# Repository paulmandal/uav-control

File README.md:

# UAV Control Link

This project is a UAV control link over a serial modem using a PlayStation 3 controller as an input.  The software produces a PPM signal output on the UAV board that can be read by typical UAV boards.

# Requirements

- [Arduino](https://www.arduino.cc/en/Main/Software)
- [Eagle](https://www.autodesk.com/products/eagle/free-download)

# Table of Contents

| Directory | Contents |
|---|----|
| js_ctrl | Takes PlayStation 3 controller input, updates its model of the airframe, relays the airframe state to joystick2ppm |
| joystick2ppm | Listens to serial traffic from js_ctrl, outputs a PPM signal based on the servo states, handles handshaking and sync |
| gcs_relay | Ground control station relay - relays traffic from js_ctrl to a serial modem |
| servotest | Decodes a PPM signal into servo outputs |

# Disclaimer

This code is old, umaintained, and probably kinda slow depending on your serial modem.  I wouldn't recommend using this to fly anything, but maybe some lessons can be learned from the code.

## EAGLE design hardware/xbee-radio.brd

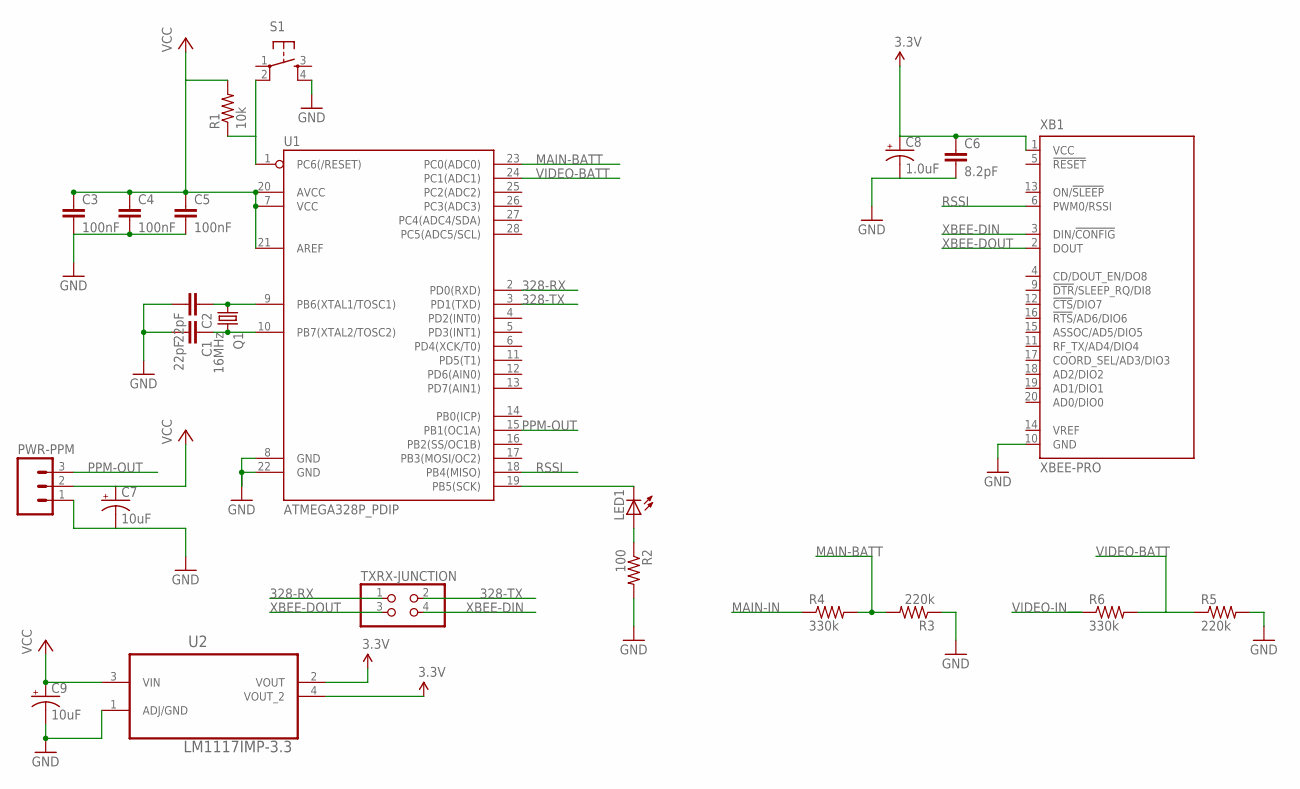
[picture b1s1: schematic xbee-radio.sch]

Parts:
C1, C2: 22pF; C2.5-2
C3, C4, C5: 100nF; C2.5-2
C6: 8.2pF; C2.5-2
C7, C9: 10uF; E2-5
C8: 1.0uF; E2-5
LED1: LED3MM
PWR-PPM: M03PTH; 1X03
Q1: 16MHz; TC26V
R1: 10k; 0204/5
R2: 100; 0204/5
R3, R5: 220k; 0204/5
R4, R6: 330k; 0204/5
S1: TAC_SWITCHPTH; TACTILE-PTH
TXRX-JUNCTION: PINHD-2X2; 2X02
U1: ATMEGA328P_PDIP; DIL28-3
U2: LM1117IMP-3.3; SOT230P696X180-4N
XB1: XBEE-PRO

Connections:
3.3V: C6.1, C8.+, U2.2 (VOUT), U2.4 (VOUT_2), XB1.1 (VCC)
328-RX: TXRX-JUNCTION.1, U1.2 (PD0(RXD))
328-TX: TXRX-JUNCTION.2, U1.3 (PD1(TXD))
GND: C1.2, C2.2, C3.2, C4.2, C5.2, C6.2, C7.-, C8.-, C9.-, PWR-PPM.1, R2.2, R3.1, R5.2, S1.4, U1.8 (GND), U1.22 (GND), U2.1 (ADJ/GND), XB1.10 (GND)
MAIN-BATT: R3.2, R4.2, U1.23 (PC0(ADC0))
MAIN-IN: R4.1
unnamed: R1.1, S1.2, U1.1 (PC6(/RESET))
unnamed: C1.1, Q1.2, U1.10 (PB7(XTAL2/TOSC2))
unnamed: C2.1, Q1.1, U1.9 (PB6(XTAL1/TOSC1))
unnamed: LED1.K (C), U1.19 (PB5(SCK))
unnamed: LED1.A, R2.1
PPM-OUT: PWR-PPM.3, U1.15 (PB1(OC1A))
RSSI: U1.18 (PB4(MISO)), XB1.6 (PWM0/RSSI)
VCC: C3.1, C4.1, C5.1, C7.+, C9.+, PWR-PPM.2, R1.2, U1.7 (VCC), U1.20 (AVCC), U1.21 (AREF), U2.3 (VIN)
VIDEO-BATT: R5.1, R6.2, U1.24 (PC1(ADC1))
VIDEO-IN: R6.1
XBEE-DIN: TXRX-JUNCTION.4, XB1.3 (DIN/!CONFIG)
XBEE-DOUT: TXRX-JUNCTION.3, XB1.2 (DOUT)

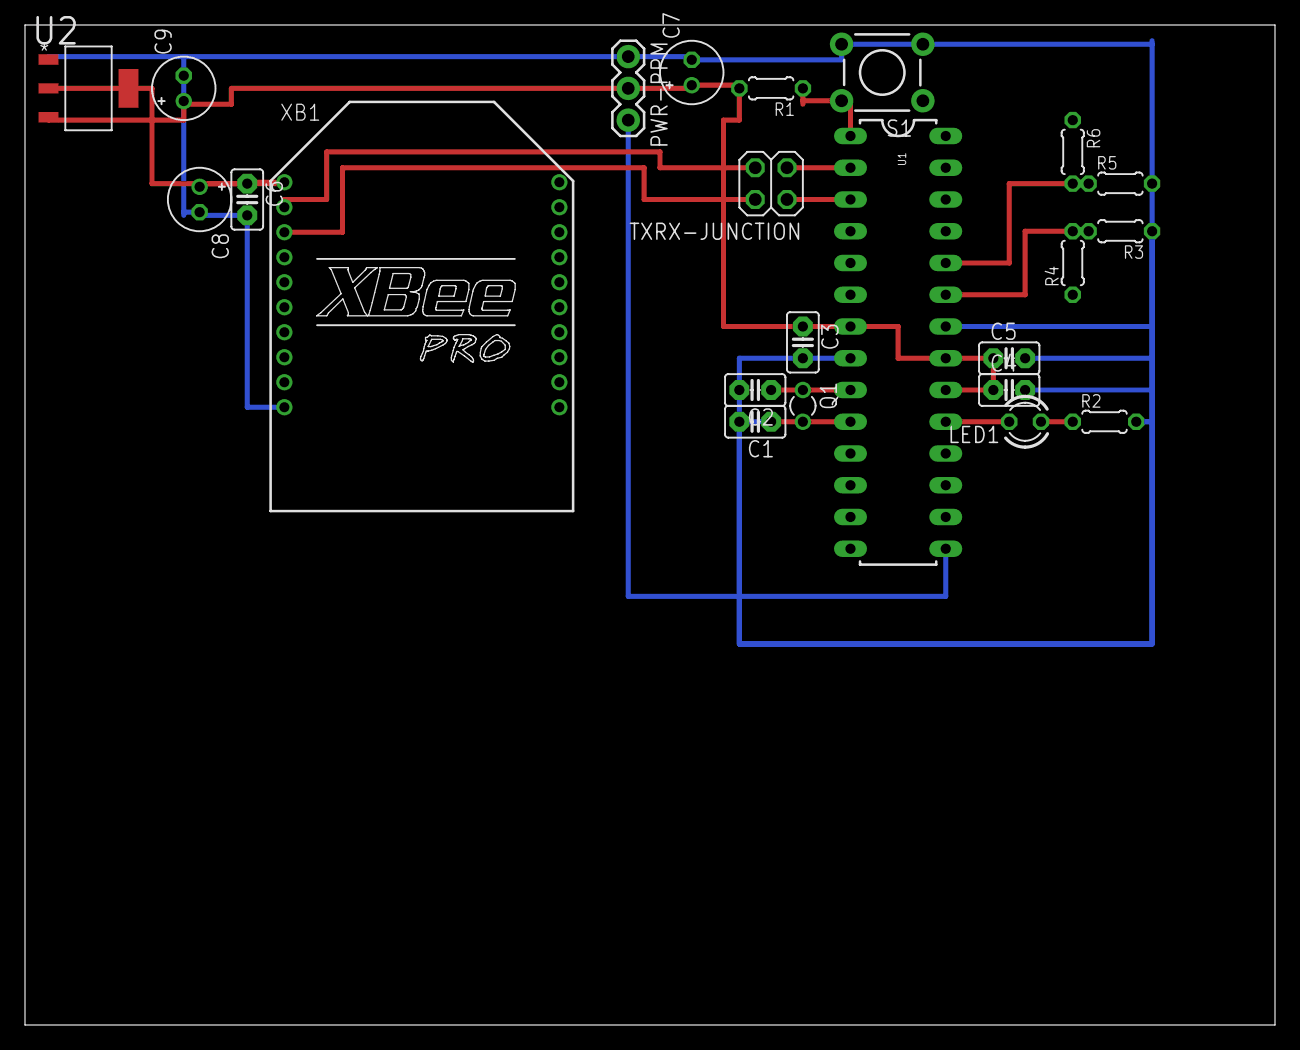
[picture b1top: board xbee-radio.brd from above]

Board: 2 copper layers, 100.0 x 80.0 mm, 23 parts (0 on the bottom side), 16 nets.

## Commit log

2011-03-24 Added main C file
2011-03-24 Added necessary .h file from jstest package
2011-03-25 Last night's build
2011-03-25 Remix\!
2011-03-26 Rewrote code.. Works now
2011-03-26 Trying to get checksum to work.. not sure
2011-03-26 Continuing, checksum in place
2011-03-30 Added latest joystick2ppm (2.0)
2011-03-30 Initial setup
2011-03-30 Added program source
2011-03-30 Updated to read from config file.
2011-03-30 Initialised config vars to NULL to get rid of de damn errors
2011-03-30 Added minor comment and updated TODO
2011-03-30 Added js_ctrl.rc file
2011-03-30 Changed version style
2011-03-31 Changed message handling, added msgType indicator
2011-03-31 Updated message handling to use msgType
2011-03-31 Tiny typo fix
2011-03-31 Fixes for msgType handling
2011-03-31 Debugging msgType handler
2011-03-31 Fixed msgType handler, stuck in loop when waiting for message, added timer with millis()
2011-03-31 Changed button config.. We should probably read this from the config file
2011-03-31 Sync msg now contains 12 random characters along with msgBegin, msgType, and checksum. This should prevent invalid sync msgs.
2011-03-31 Added sync with checksum reply instead of silly ACK
2011-03-31 Added sync with checksum instead of silly simple ACK
2011-03-31 msgType handling, and ACK with checksum
2011-03-31 Worked on msgType stuff, this doesn't work, handshake works but no control updates
2011-03-31 This does work, however, that does not make any sense to me.
2011-03-31 Uncommented handshaking progress display period
2011-03-31 Figured out why
2011-03-31 Better message handling, need to debug
2011-03-31 Better message handling, will improve moar
2011-03-31 Updated version #
2011-03-31 Updated comms to reflect new style
2011-03-31 Debugged port from Arduino
2011-03-31 Debugged new comms metho
2011-03-31 Debugged new comms method
2011-03-31 Fixed XBee post-sync garbage message
2011-03-31 Fixed new messaging system
2011-03-31 Fixed minor messages
2011-03-31 Changed toggle button for nav lights
2011-04-01 Finished working here for now
2011-04-01 Removed ugly global vars, pre-debug
2011-04-01 Debugging
2011-04-01 Debugging almost done..
2011-04-01 Updated with new signal sync and removed fugly global vars
2011-04-01 Added ACK every 50 commands
2011-04-01 Done with sync work
2011-04-01 Added new todos
2011-04-01 Done for the night, PPM off when desynched on either side, perfectuamundo.
2011-04-01 Fixed memory slapping
2011-04-01 Fixed a memory leak
2011-04-01 Fixed global vars
2011-04-01 Removed fgly vars
2011-04-01 Debug messages in place, now just to figure it all out
2011-04-02 Next debug iteration
2011-04-02 Almost done debugging
2011-04-02 Deep in the debugging now
2011-04-02 Moar debugging progress
2011-04-02 Found the error.. Some disturbing info about having 2 serials, it may f up the interrupts..it was causing the chip to fail to receive properly
2011-04-02 Trying out a theory.. changed control interrupt to 75Hz instead of 100Hz.. may ditch it entirely in favour of having processMessage() handle the updates as they come.. I'd also like to make the timer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
2011-04-02 Disabled servo update timer as test
2011-04-02 Still dropping stuff..Trying both ports at same speed
2011-04-02 Still dropping stuff..Trying both ports at same speed 115200
2011-04-02 Ditched Timer2 for servo updates - updated on received command (should be 50Hz), too many interrupts.. next is to get Timer1 to switch the pin state correctly so we can short its interrupt code
2011-04-02 Done with ifdef and debug, time to try Timer stuff
2011-04-02 Fixed bug, no prototype for handleControlUpdate() function, also no compiler error >_<
2011-04-02 That worked better than I thought
2011-04-02 Getting PPM to be done by hardware was easier than I thought.. Now just to clean up the ISR() for Timer1, modify the way pulses are stored (store sync pulses and such) and test error conditions (disc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
2011-04-02 Disabled output pin on lostSignal.. now I have to figure out how to keep the signal from getting inverted
2011-04-02 Okay, disable the output pin for real this time
2011-04-02 Got PPM working except it inverts sometimes, gotta figure out invert
2011-04-02 Okay, everything looks good except the invert
2011-04-02 Trying to reset timer each time to avoid invert
2011-04-02 Continuing to fight signal inversion issue.. now with moar knowledgecules\!
2011-04-02 Almost done with inverted signal fix
2011-04-02 w00t consistent non-inverted PPM signal
2011-04-02 Updated version to reflect new code
2011-04-03 Reworked the loop a bit, brought CPU usage (single core) from 50% to 8%.. still a bit high
2011-04-03 Put in another delay, worked the CPU usage down to 4% which is acceptable
2011-04-03 Updated version number to reflect fixes
2011-04-03 Changed a function name
2011-04-05 Pre-debug commit
2011-04-06 Finished debugging
2011-04-06 Done debugging for now, need to test when USB->TTL arrives
2011-04-06 Commit to switch branches
2011-04-06 Made struct names cooler
2011-04-06 Debug finished
2011-04-06 Finished make.. trying autoindent
2011-04-07 Blah
2011-04-07 Msg fixed
2011-04-07 Reordered file
2011-04-07 Weird merge
2011-04-07 Fixed a bunch of things.. it actually compiles now, for one
2011-04-07 Fixed
2011-04-07 Reordered functions
2011-04-07 Bugfixes
2011-04-07 Cleaned up debug
2011-04-07 Changes USB
2011-04-07 Continuing work without TTL :(
2011-04-08 Minor changes
2011-04-08 Testing
2011-04-08 Weird testing
2011-04-08 Fixed minor bug
2011-04-18 Finished debugging USB devices
2011-04-18 Minor cleanup
2011-04-18 Finished debugging new stuff
2011-04-19 Some debug code
2011-04-19 Fugly fix for inverted PPM
2011-04-19 Nightnight
2011-04-20 TODO: msg<->ppz, debug msg over serial1, fix debug msg handling
2011-04-20 Maekd more changes, pre-debug commit, messaging system updated
2011-04-20 Made changes to message handling, pre-debug commit
2011-04-21 Post-debug commit
2011-04-21 Post-debug commit, still resets sometimes
2011-04-21 Debug commit
2011-04-21 Clean commit
2011-04-26 Did things
2011-04-26 Trying to keep PPM signal good
2011-04-26 Preparing for 328 branch
2011-04-26 Added 328P mode
2011-04-26 Pre-debug pty commit
2011-04-26 More pre-debug stuff
2011-04-26 Fixed some compilation errors
2011-04-26 Pre debug commit
2011-04-26 More debuggin
2011-04-27 Pty works
2011-04-27 Updated version
2011-04-27 Removed debug line
2011-04-27 Pre debug commit 2
2011-04-28 Forcing feedbacks
2011-04-29 Ditched dpad, switched to context swapping and joysticks for camera control
2011-04-29 Cleaned up debugging stuff
2011-04-29 Pinout pre-debug
2011-04-30 Ugh error was introduced
2011-04-30 Fixed dbgMsg issue
2011-04-30 Fixed error - pin 14 should be Analog 0 but instead looped back to Digital 0 - messing with the TX pin
2011-05-03 Pre-debug force feedback
2011-05-03 Compiler errors fixed, need to debug with controller
2011-05-04 FF works, need to adjust settings
2011-05-04 Added 9 levels of rumble
2011-05-04 Typo bugfix
2011-05-04 Gotta decide on proper levels for rumble, but it's coming
2011-05-05 Got good rumble ramping, probably switch to 4-15 as signallost, 0-3 as signal weak
2011-05-05 Fixed PPM length, was prescaler 8 = 2mhz not 1mhz
2011-05-05 Kickass
2011-05-05 Servo change for mucking
2011-05-05 Minor version change
2011-05-05 Debugging argh
2011-05-05 Servo directly from control
2011-05-05 Moar work
2011-05-06 Physical test begins
2011-05-06 Begin physical testing
2011-06-22 Made flashing lights more memory efficient
2011-06-25 Pre debug commit, update messaging/signaling
2011-06-25 More pre-debug work
2011-06-25 Almost done reworking message system
2011-06-28 Fixed compile errors, debugging
2011-06-28 Still debugging, servo updates are not working
2011-06-29 Your chart says you're fucked up.. you need your messaging fixed
2011-06-30 Done with this branch
2011-07-01 Yarn
2011-07-02 More works, added basic output
2011-07-02 Minor debugging/testing with protoboard
2011-07-04 Initialised repo
2011-07-04 First added
2011-07-05 Did a bunch of things, display buffers and display system, more batteries, mtype enums
2011-07-05 Done with message buffer basics.
2011-07-05 Debugged, kickass
2011-07-05 Got PPM read and servo resolution to .5usec
2011-07-06 Added config via msg, pre-debug commit
2011-07-06 Debugging over, appears good
2011-07-06 Debugged sending config via msg, seems good, even takes new config while running
2011-07-06 Forgot to add PPM Sync Pulse to config
2011-07-08 Proto-2.0 testing
2011-07-11 More debugging with hardware 2.0
2011-07-12 Added program
2011-07-13 Finished debugging RSSI circuit stuff
2011-07-16 Basic ncurses implemented, dirty dirty dirty
2011-07-18 Reorganized repo, removed duplicate files, removed object files
2011-07-18 Renamed README->README.md
2011-07-18 Removed README
2013-04-04 Added initial files
2013-04-05 Added test circuit diagrams

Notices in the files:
parts and their libraries:
SparkFun-DigitalIC: Licensing: CC v3.0 Share-Alike You are welcome to use this library for commercial purposes.
